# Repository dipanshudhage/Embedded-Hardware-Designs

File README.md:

# Embedded-Hardware-Designs

A collection of KiCad schematics, PCB layouts, 3D renders, STEP models, and hardware design files covering microcontroller boards, power/switching modules, USB-serial interfaces, LED controllers, and analog circuits.

## Repository Contents

| Folder | Description | Documentation & Assets |
| :--- | :--- | :--- |
| `ARDUINO MCU BOARD` | Microcontroller board design | [Project README](ARDUINO%20MCU%20BOARD/README.md) · `ASSETS/` |
| `ARDUINO PRO MINI` | Compact Arduino Pro Mini hardware layout | [Project README](ARDUINO%20PRO%20MINI/README.md) · `ASSETS/` · `.csv` |
| `LED` | LED circuit schematic, PCB layout, and 3D views | [Project README](LED/README.md) · `ASSETS/` |
| `LED FLASHING CIRCUIT` | Flashing LED circuit schematic and layout | [Project README](LED%20FLASHING%20CIRCUIT/README.md) · `ASSETS/` |
| `LED sequential flasher` | Sequential LED flasher circuit design | [Project README](LED%20sequential%20flasher/README.md) · `ASSETS/` |
| `Light-Activated LED Controller` | Light-triggered LED control circuit | [Project README](Light-Activated%20LED%20Controller/README.md) · `ASSETS/` |
| `Qwiic_Power_Switch` | Power switching hardware module | [Project README](Qwiic_Power_Switch/README.md) · `Assets/` |
| `SMART NODE – ESP32 ROOM CONTROLLER` | ESP32-based room controller hardware design | [Project README](SMART%20NODE%20%E2%80%93%20ESP32%20ROOM%20CONTROLLER/README.md) · `ASSETS/` |
| `Serial-Basic-CH340C-and-USBC` | USB-C to UART serial interface using CH340C | [Project README](Serial-Basic-CH340C-and-USBC/README.md) · `Assets/` |
| `TSH82 Configurable Op-Amp Board` | Configurable operational amplifier board using TSH82 | [Project README](TSH82%20Configurable%20Op-Amp%20Board/README.md) · `Assets/` |

## Tools & Workflow
* **EDA Suite:** KiCad (`.kicad_pro`, `.kicad_sch`, `.kicad_pcb`)
* **Visuals & 3D CAD:** Schematic, layout, and front/back 3D PNG renders plus `.step` 3D models

## How to Use
1. Browse any project folder's `README.md` for a quick look at its schematic, PCB layout, and 3D front/back views.
2. Open the `.kicad_pro` file in **KiCad** to inspect schematics, footprints, and board layouts.
3. Run Electrical Rule Checks (ERC) and Design Rule Checks (DRC) and verify component ratings/footprints before fabrication or assembly.

## Hardware & Safety Disclaimer
These schematic, PCB, and hardware files are shared for educational, learning, and prototyping purposes. Always review schematics, power ratings, isolation clearances, and component datasheets carefully before powering up or manufacturing any circuit.

## License
This repository is licensed under the **MIT License** — see the [`LICENSE`](LICENSE) file for details.

## Author
**Dipanshu Dhage**

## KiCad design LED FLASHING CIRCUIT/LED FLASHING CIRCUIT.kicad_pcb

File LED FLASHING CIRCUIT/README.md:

# LED FLASHING CIRCUIT

## Overview
LED flashing circuit designed in KiCad with schematic, board layout, and 3D renders.

## Schematic & PCB Layout

## 3D Board Views
| Front View | Back View |
| :---: | :---: |
|  |  |

## 3D CAD Model
* STEP Model: [`LED FLASHING CIRCUIT.step`](ASSETS/LED%20FLASHING%20CIRCUIT.step)

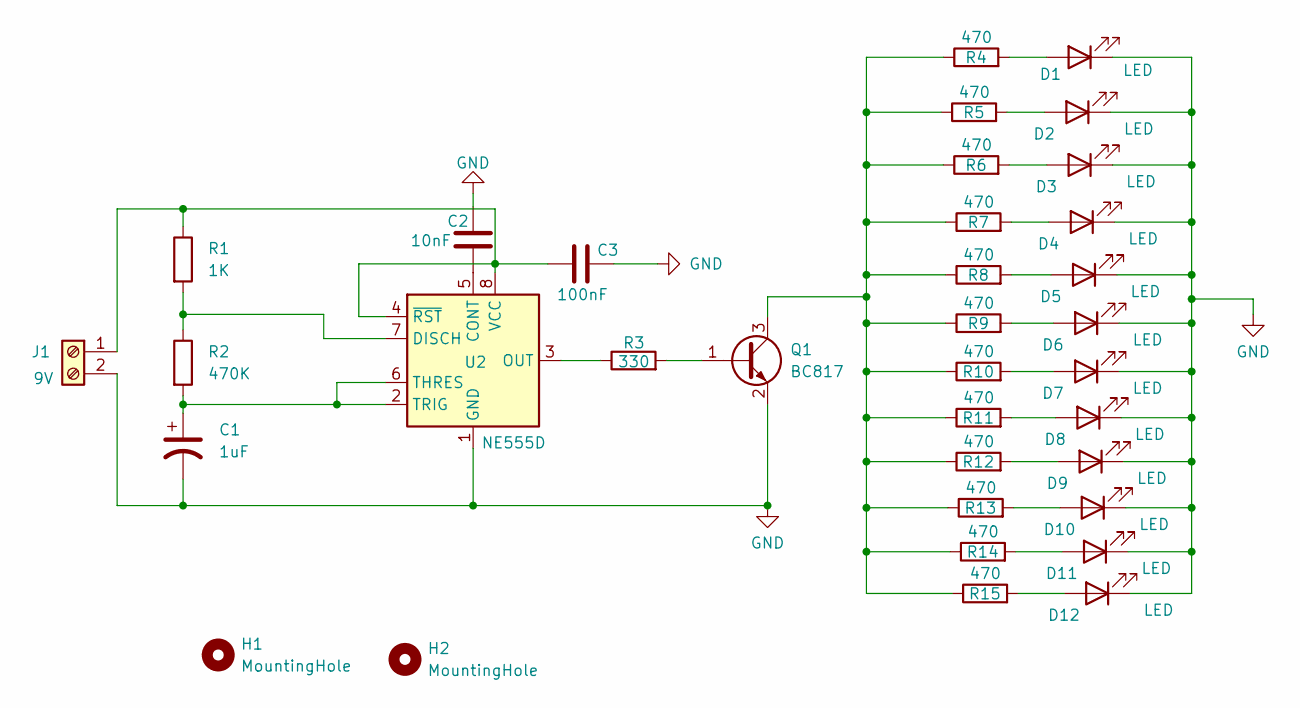
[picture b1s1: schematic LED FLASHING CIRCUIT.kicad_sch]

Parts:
C1: 1uF; C_0805_2012Metric
C2: 10nF; C_0805_2012Metric
C3: 100nF; C_0805_2012Metric
D1, D2, D3, D4, D5, D6, D7, D8, D9, D10, D11, D12: LED; LED_0805_2012Metric
H1, H2: MountingHole; MountingHole_2.2mm_M2
J1: 9V; JST_EH_S2B-EH_1x02_P2.50mm_Horizontal
Q1: BC817; SOT-23
R1: 1K; R_0805_2012Metric
R2: 470K; R_0805_2012Metric
R3: 330; R_0805_2012Metric
R4, R5, R6, R7, R8, R9, R10, R11, R12, R13, R14, R15: 470; R_0805_2012Metric
U2: NE555D; SOIC-8_3.9x4.9mm_P1.27mm

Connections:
GND: C1.2, C2.1, C3.1, D1.1 (K), D2.1 (K), D3.1 (K), D4.1 (K), D5.1 (K), D6.1 (K), D7.1 (K), D8.1 (K), D9.1 (K), D10.1 (K), D11.1 (K), D12.1 (K), J1.2, Q1.2 (E), U2.1 (GND)
unnamed: D1.2 (A), R4.2
unnamed: D2.2 (A), R5.2
unnamed: D3.2 (A), R6.2
unnamed: D4.2 (A), R7.2
unnamed: D5.2 (A), R8.2
unnamed: D6.2 (A), R9.2
unnamed: D7.2 (A), R10.2
unnamed: D8.2 (A), R11.2
unnamed: D9.2 (A), R12.2
unnamed: D10.2 (A), R13.2
unnamed: D11.2 (A), R14.2
unnamed: D12.2 (A), R15.2
unnamed: C3.2, J1.1, R1.1, U2.4 (~RST), U2.8 (VCC)
unnamed: Q1.1 (B), R3.2
unnamed: Q1.3 (C), R4.1, R5.1, R6.1, R7.1, R8.1, R9.1, R10.1, R11.1, R12.1, R13.1, R14.1, R15.1
unnamed: C2.2, U2.5 (CONT)
unnamed: R1.2, R2.1, U2.7 (DISCH)
unnamed: R3.1, U2.3 (OUT)
unnamed: C1.1, R2.2, U2.2 (TRIG), U2.6 (THRES)

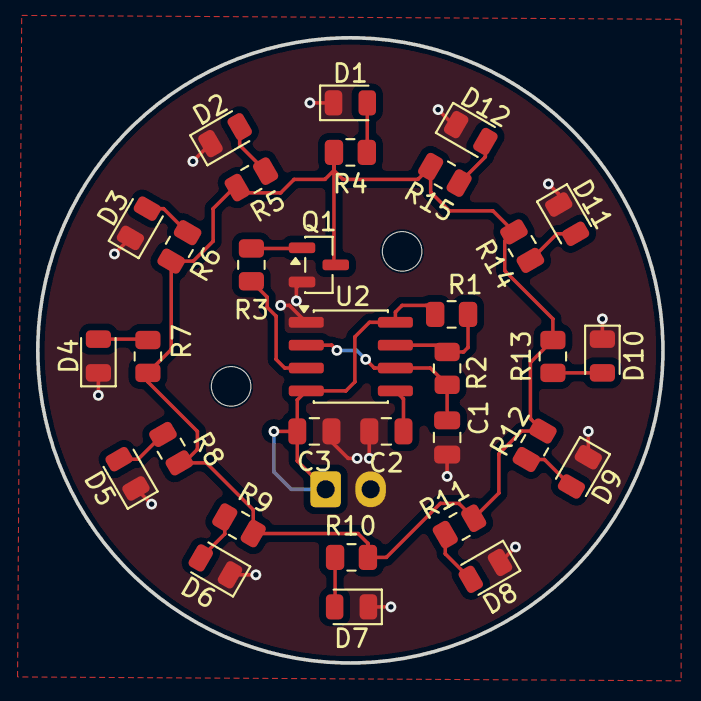
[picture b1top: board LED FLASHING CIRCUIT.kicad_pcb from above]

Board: 2 copper layers, 34.7 x 34.7 mm, 35 parts (1 on the bottom side), 20 nets.

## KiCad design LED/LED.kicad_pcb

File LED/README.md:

# LED

## Overview
LED hardware circuit design in KiCad with schematic, layout, and 3D views.

## Schematic & PCB Layout

## 3D Board Views
| Front View | Back View |
| :---: | :---: |
|  |  |

## 3D CAD Model
* STEP Model: [`LED.step`](ASSETS/LED.step)

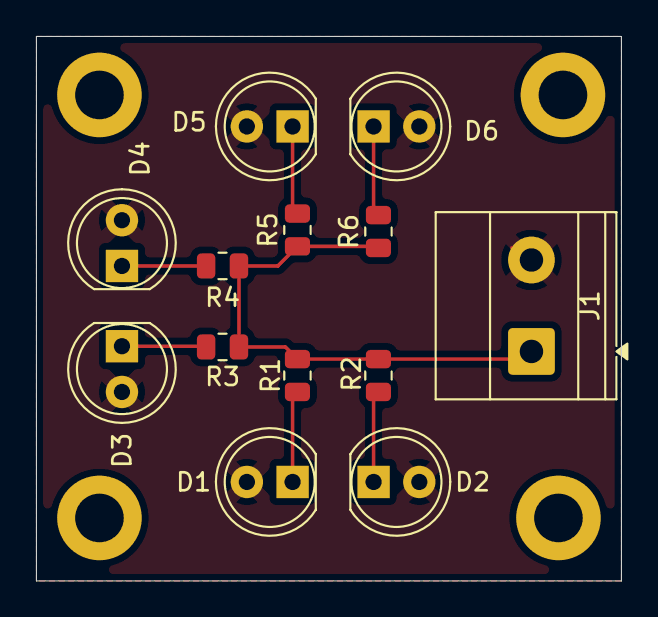
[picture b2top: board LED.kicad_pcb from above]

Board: 2 copper layers, 32.5 x 30.2 mm, 17 parts (0 on the bottom side), 8 nets.

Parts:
D1, D2, D3, D4, D5, D6: LED; LED_D5.0mm
H4, H4#2, H4#3, H4#4: MountingHole; MountingHole_2.7mm_M2.5_DIN965_Pad
J1: Power Source; TerminalBlock_Phoenix_MKDS-1,5-2-5.08_1x02_P5.08mm_Horizont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
R1, R2, R3, R4, R5, R6: 15; R_0805_2012Metric

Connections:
+3.3V: J1.1, R1.1, R2.1, R3.1, R4.1, R5.1, R6.1
GND: D1.2 (A), D2.2 (A), D3.2 (A), D4.2 (A), D5.2 (A), D6.2 (A), J1.2
unnamed: D1.1 (K), R1.2
unnamed: D2.1 (K), R2.2
unnamed: D3.1 (K), R3.2
unnamed: D4.1 (K), R4.2
unnamed: D5.1 (K), R5.2
unnamed: D6.1 (K), R6.2

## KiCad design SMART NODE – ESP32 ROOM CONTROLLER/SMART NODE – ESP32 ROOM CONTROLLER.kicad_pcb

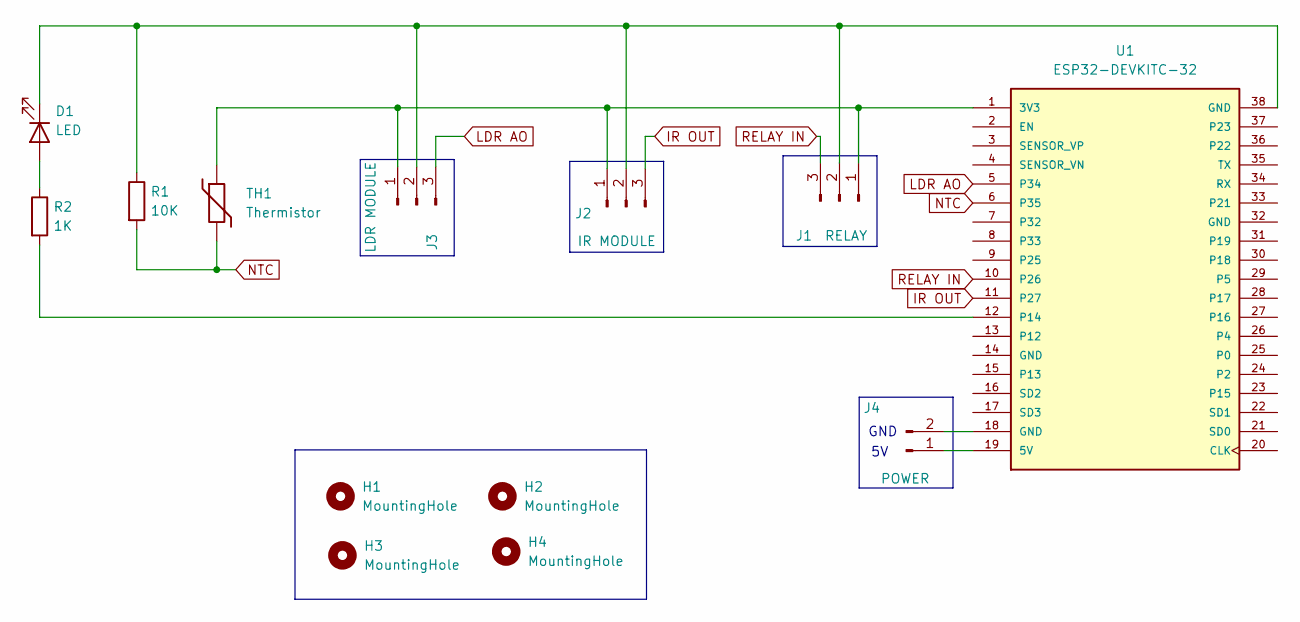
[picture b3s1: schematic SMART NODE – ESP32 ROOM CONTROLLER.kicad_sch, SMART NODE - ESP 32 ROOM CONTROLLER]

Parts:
D1: LED; LED_D5.0mm
H1, H2, H3, H4: MountingHole; MountingHole_2.2mm_M2
J1: RELAY; PinSocket_1x03_P2.54mm_Vertical
J2: IR MODULE; PinSocket_1x03_P2.54mm_Vertical
J3: LDR MODULE; PinSocket_1x03_P2.54mm_Vertical
J4: POWER; TerminalBlock_Phoenix_MKDS-1,5-2_1x02_P5.00mm_Horizontal
R1: 10K; R_Axial_DIN0207_L6.3mm_D2.5mm_P10.16mm_Horizontal
R2: 1K; R_Axial_DIN0207_L6.3mm_D2.5mm_P10.16mm_Horizontal
TH1: Thermistor; C_Disc_D5.0mm_W2.5mm_P2.50mm
U1: ESP32-DEVKITC-32; ESP32 DEVKIT

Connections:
IR OUT: J2.3, U1.11 (P27)
LDR AO: J3.3, U1.5 (P34)
NTC: R1.2, TH1.2, U1.6 (P35)
unnamed: D1.2 (A), R2.1
unnamed: D1.1 (K), J1.2, J2.2, J3.2, R1.1, U1.38 (GND)
unnamed: J1.1, J2.1, J3.1, TH1.1, U1.1 (3V3)
unnamed: J4.1, U1.19 (5V)
unnamed: J4.2, U1.18 (GND)
unnamed: R2.2, U1.12 (P14)
RELAY IN: J1.3, U1.10 (P26)

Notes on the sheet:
GND

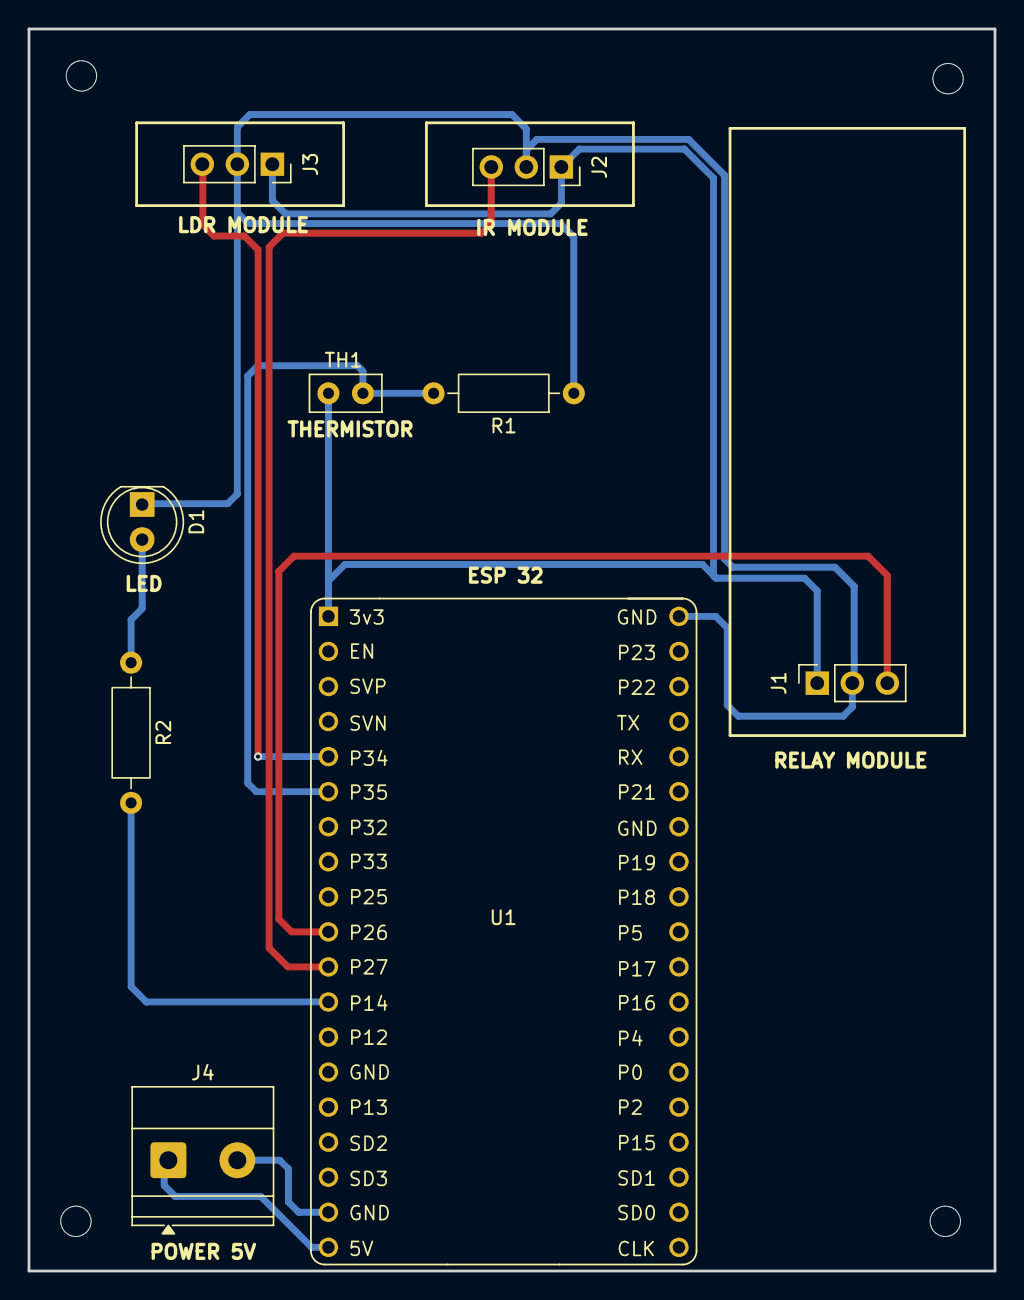
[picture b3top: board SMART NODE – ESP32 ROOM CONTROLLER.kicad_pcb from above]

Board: 2 copper layers, 70.0 x 90.0 mm, 13 parts (0 on the bottom side), 10 nets.

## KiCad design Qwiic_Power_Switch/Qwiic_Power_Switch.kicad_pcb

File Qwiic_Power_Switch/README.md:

# Qwiic_Power_Switch

## Overview
Power switching hardware module with schematic, PCB layout, and 3D views.

## Schematic & PCB Layout

## 3D Board Views
| Front View | Back View |
| :---: | :---: |
|  |  |

## 3D CAD Model
* STEP Model: [`Qwiic_Power_Switch.step`](Assets/Qwiic_Power_Switch.step)

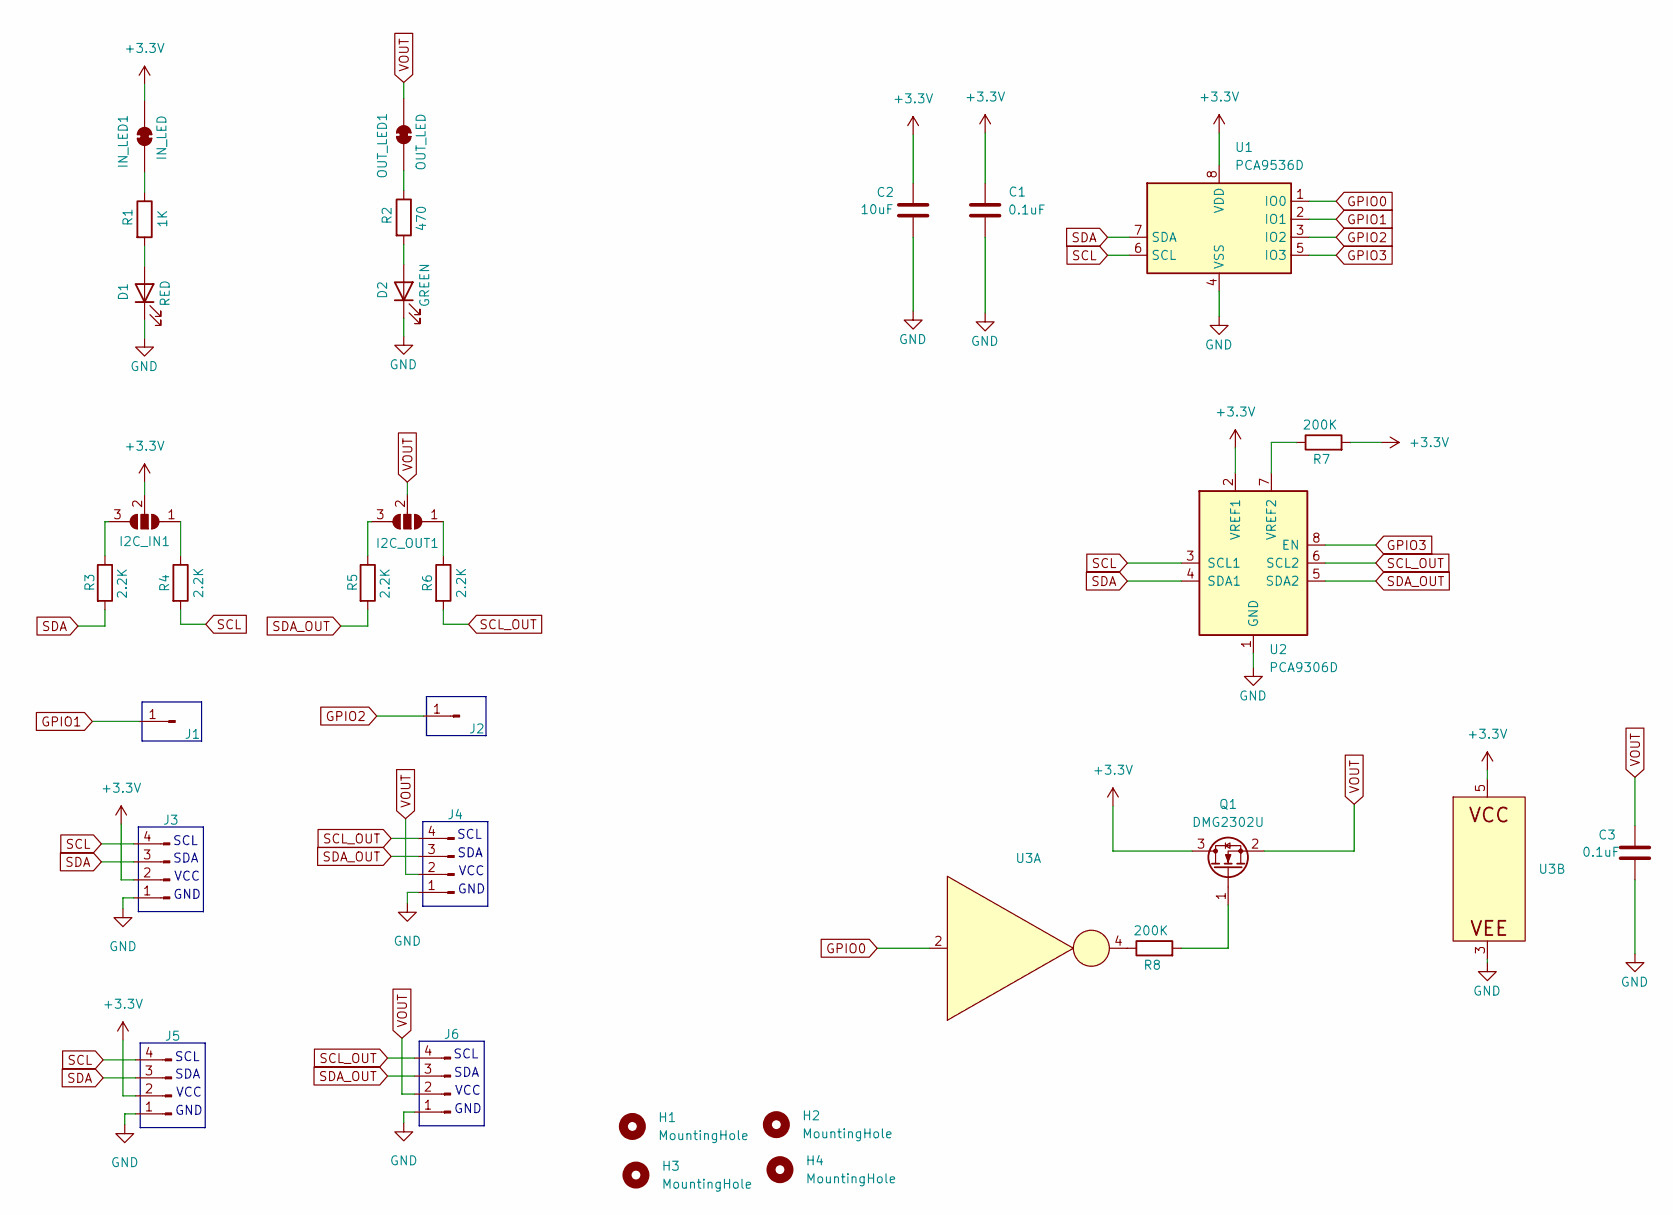
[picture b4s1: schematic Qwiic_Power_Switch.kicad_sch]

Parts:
C1, C3: 0.1uF; C_0603_1608Metric
C2: 10uF; C_0805_2012Metric
D1: RED; LED_0603_1608Metric
D2: GREEN; LED_0603_1608Metric
H1, H2, H3, H4: MountingHole; MountingHole_2.2mm_M2
I2C_IN1, I2C_OUT1: SolderJumper_3_Open; SolderJumper-3_P1.3mm_Open_Pad1.0x1.5mm
IN_LED1: IN_LED; LED_0603_1608Metric
J1, J2: Conn_01x01_Pin; PinHeader_1x01_P2.54mm_Vertical
J3, J4, J5, J6: Conn_01x04_Pin; PinSocket_1x04_P2.54mm_Vertical
OUT_LED1: OUT_LED; LED_0603_1608Metric
Q1: DMG2302U; SOT-23
R1: 1K; R_0603_1608Metric
R2: 470; R_0603_1608Metric
R3, R4, R5, R6: 2.2K; R_0603_1608Metric
R7, R8: 200K; R_0603_1608Metric
U1: PCA9536D; SOIC-8_3.9x4.9mm_P1.27mm
U2: PCA9306D; SO-8_3.9x4.9mm_P1.27mm
U3: SOT-353_SC-70-5

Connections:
+3.3V: C1.1, C2.1, I2C_IN1.2 (C), IN_LED1.2 (B), J3.2, J5.2, Q1.3 (D), R7.2, U1.8 (VDD), U2.2 (VREF1), U3.5
GND: C1.2, C2.2, C3.2, D1.1 (K), D2.1 (K), J3.1, J4.1, J5.1, J6.1, U1.4 (VSS), U2.1 (GND), U3.3
GPIO0: U1.1 (IO0), U3.2
GPIO1: J1.1 (Pin_1_1), U1.2 (IO1)
GPIO2: J2.1 (Pin_1_1), U1.3 (IO2)
GPIO3: U1.5 (IO3), U2.8 (EN)
unnamed: D1.2 (A), R1.2
unnamed: D2.2 (A), R2.2
unnamed: I2C_IN1.1 (A), R4.1
unnamed: I2C_IN1.3 (B), R3.1
unnamed: I2C_OUT1.1 (A), R6.1
unnamed: I2C_OUT1.3 (B), R5.1
unnamed: IN_LED1.1 (A), R1.1
unnamed: OUT_LED1.1 (A), R2.1
unnamed: Q1.1 (G), R8.2
unnamed: R8.1, U3.4
unnamed: R7.1, U2.7 (VREF2)
SCL: J3.4, J5.4, R4.2, U1.6 (SCL), U2.3 (SCL1)
SCL_OUT: J4.4, J6.4, R6.2, U2.6 (SCL2)
SDA: J3.3, J5.3, R3.2, U1.7 (SDA), U2.4 (SDA1)
SDA_OUT: J4.3, J6.3, R5.2, U2.5 (SDA2)
VOUT: C3.1, I2C_OUT1.2 (C), J4.2, J6.2, OUT_LED1.2 (B), Q1.2 (S)

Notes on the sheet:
VCC
SDA
SCL
GND

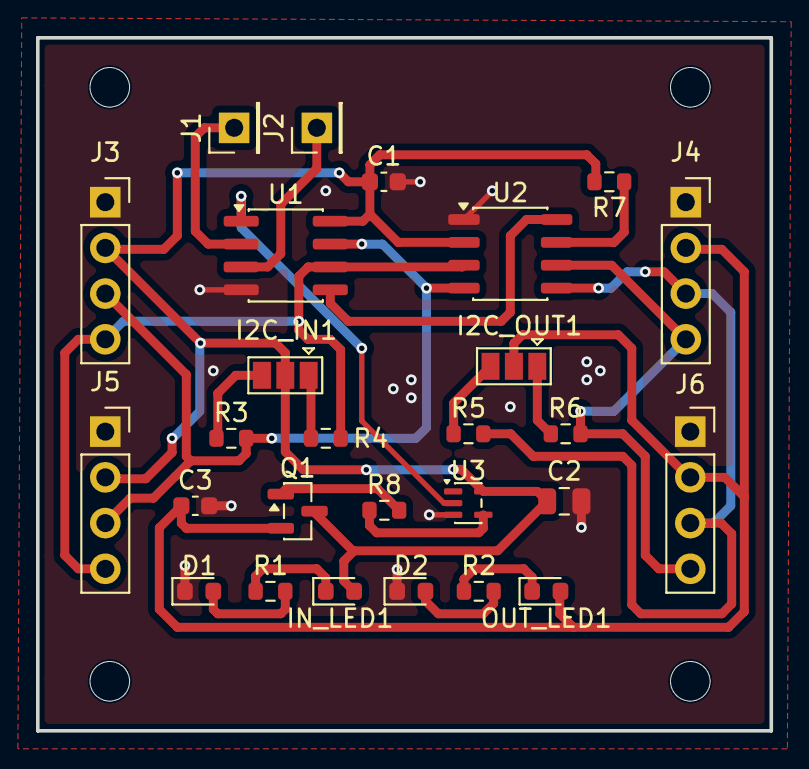
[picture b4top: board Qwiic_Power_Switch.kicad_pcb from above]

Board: 2 copper layers, 40.8 x 38.5 mm, 31 parts (0 on the bottom side), 22 nets.

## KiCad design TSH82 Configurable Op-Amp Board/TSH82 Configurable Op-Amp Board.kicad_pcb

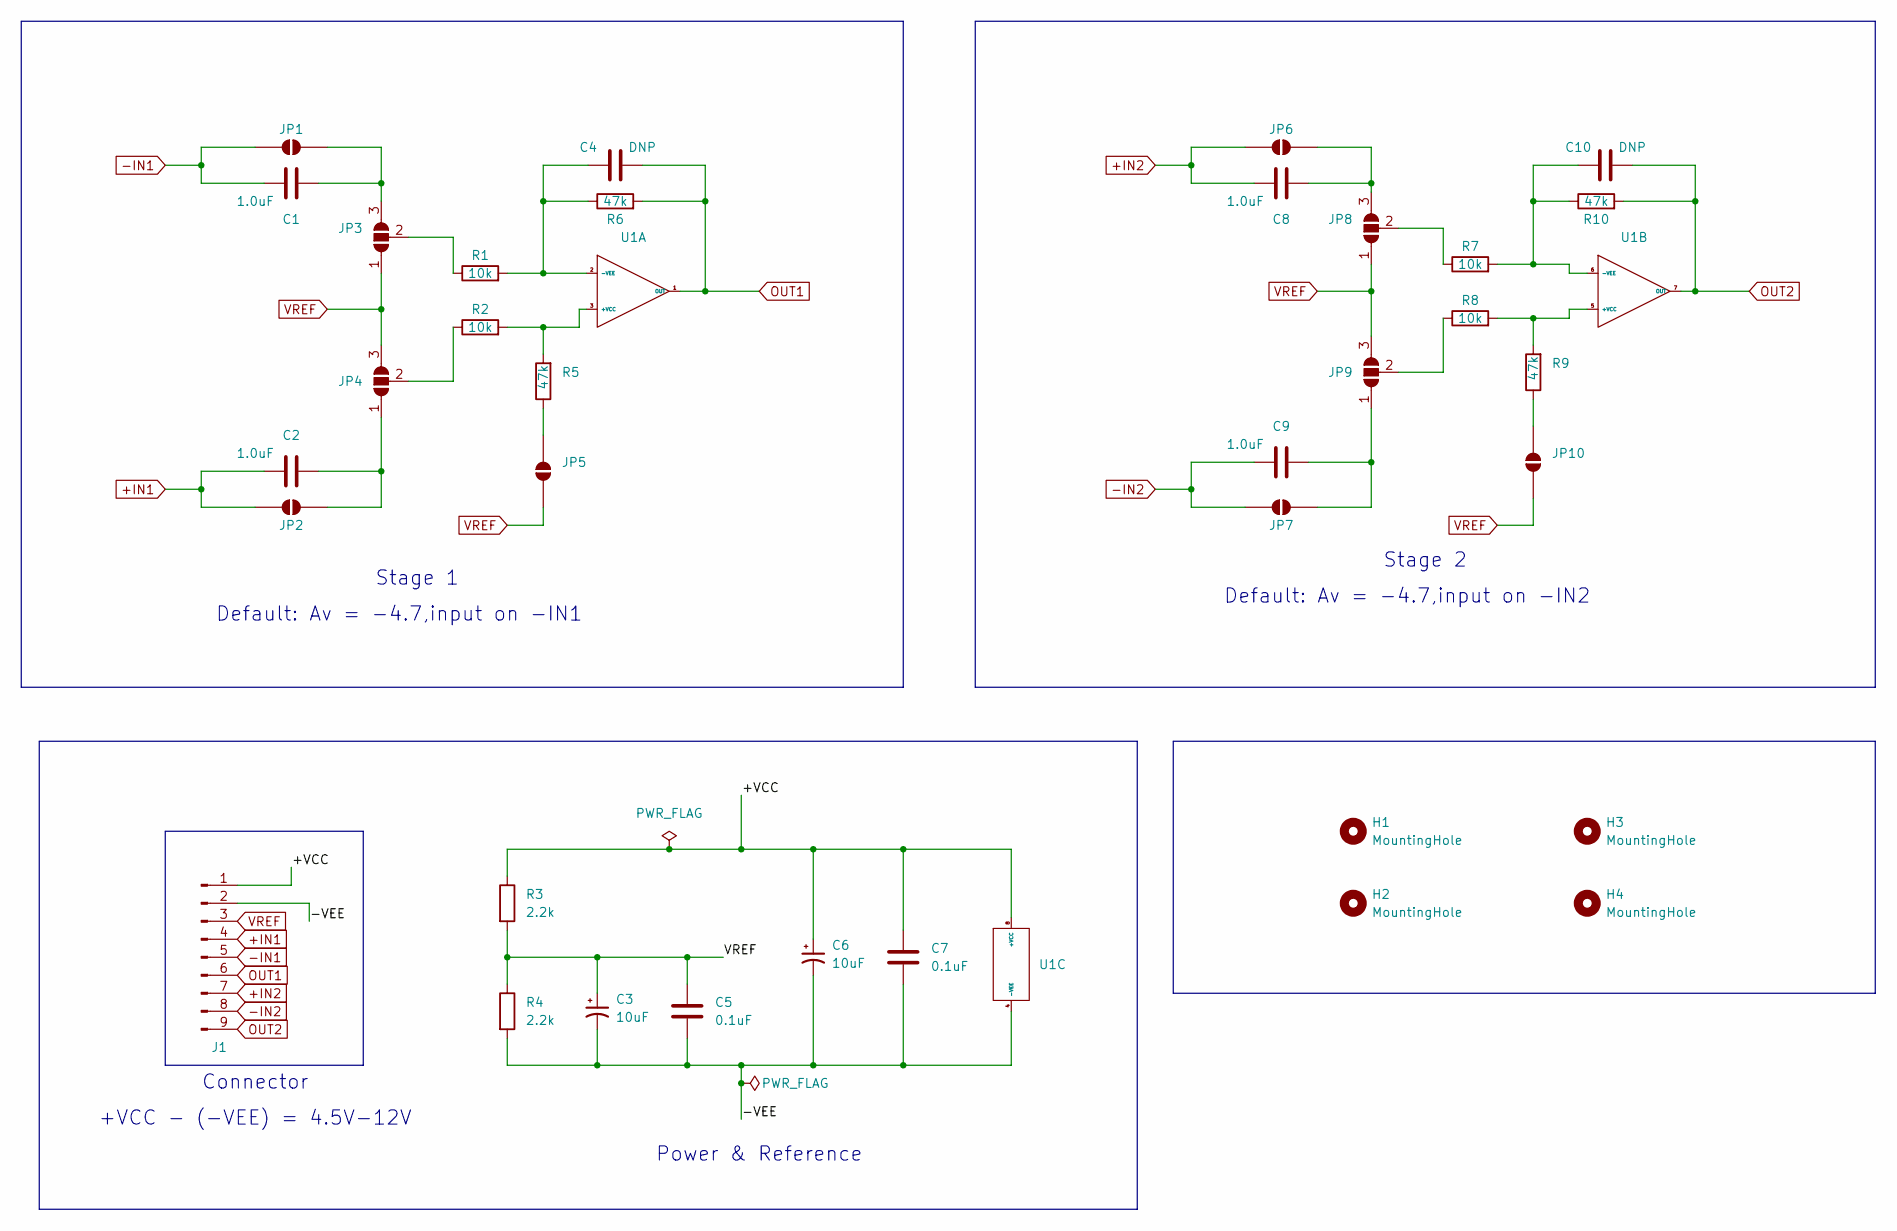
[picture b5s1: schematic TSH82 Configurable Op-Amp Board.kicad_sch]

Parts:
C1, C2, C8, C9: 1.0uF; C_0805_2012Metric
C3, C6: 10uF; C_1206_3216Metric
C4, C10: DNP; C_0805_2012Metric
C5, C7: 0.1uF; C_0805_2012Metric
H1, H2, H3, H4: MountingHole; MountingHole_2.7mm
J1: Conn_01x09_Pin; PinHeader_1x09_P2.54mm_Vertical
JP1, JP5, JP6, JP10: SolderJumper_2_Open; SolderJumper-2_P1.3mm_Open_Pad1.0x1.5mm
JP2, JP7: SolderJumper-2_P1.3mm_Open_Pad1.0x1.5mm
JP3, JP4, JP8, JP9: SolderJumper_3_Open; SolderJumper-3_P1.3mm_Open_Pad1.0x1.5mm
R1, R2, R7, R8: 10k; R_0805_2012Metric
R3, R4: 2.2k; R_0805_2012Metric
R5, R6, R9, R10: 47k; R_0805_2012Metric
U1: SOIC-8_3.9x4.9mm_P1.27mm

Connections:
+IN1: C2.1, J1.4, JP2.1 (A)
+IN2: C8.1, J1.7, JP6.1 (A)
-IN1: C1.1, J1.5, JP1.1 (A)
-IN2: C9.1, J1.8, JP7.1 (A)
/+VCC: C6.1, C7.1, J1.1, R3.1, U1.8 (+VCC)
/-VEE: C3.2, C5.2, C6.2, C7.2, J1.2, R4.2, U1.4 (-VEE)
unnamed: C1.2, JP1.2 (B), JP3.3 (B)
unnamed: C2.2, JP2.2 (B), JP4.1 (A)
unnamed: JP3.2 (C), R1.1
unnamed: JP4.2 (C), R2.1
unnamed: JP5.2 (B), R5.1
unnamed: C8.2, JP6.2 (B), JP8.3 (B)
unnamed: C9.2, JP7.2 (B), JP9.1 (A)
unnamed: JP8.2 (C), R7.1
unnamed: JP9.2 (C), R8.1
unnamed: JP10.2 (B), R9.1
unnamed: R2.2, R5.2, U1.3 (+VCC)
unnamed: C4.1, R1.2, R6.1, U1.2 (-VEE)
unnamed: R8.2, R9.2, U1.5 (+VCC)
unnamed: C10.1, R7.2, R10.1, U1.6 (-VEE)
OUT1: C4.2, J1.6, R6.2, U1.1 (OUT)
OUT2: C10.2, J1.9, R10.2, U1.7 (OUT)
VREF: C3.1, C5.1, J1.3, JP3.1 (A), JP4.3 (B), JP5.1 (A), JP8.1 (A), JP9.3 (B), JP10.1 (A), R3.2, R4.1

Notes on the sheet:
Default: Av = -4.7,input on -IN2
Stage 2
Connector
+VCC - (-VEE) = 4.5V-12V
Default: Av = -4.7,input on -IN1
Power & Reference
Stage 1

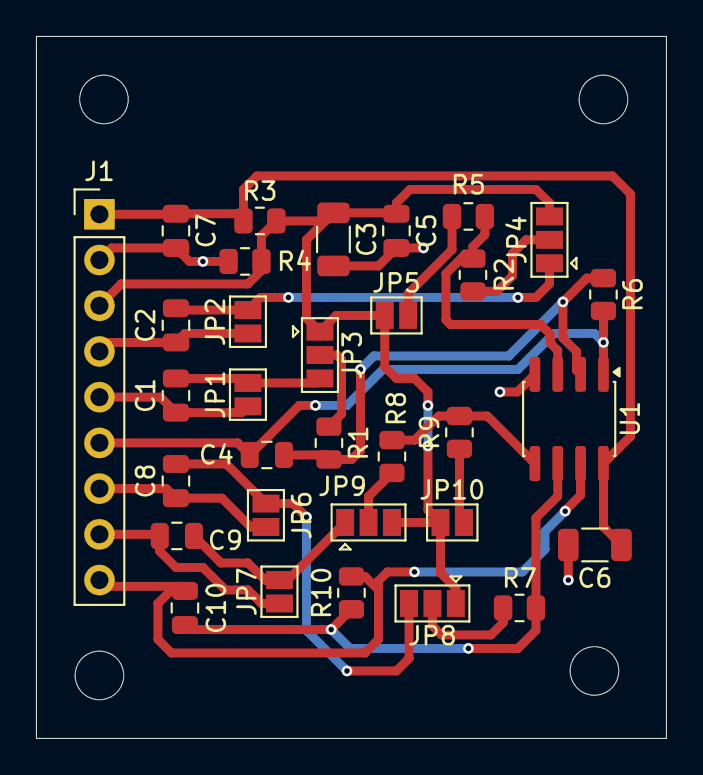
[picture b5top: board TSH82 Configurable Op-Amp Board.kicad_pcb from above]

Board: 2 copper layers, 35.0 x 39.0 mm, 36 parts (0 on the bottom side), 23 nets.

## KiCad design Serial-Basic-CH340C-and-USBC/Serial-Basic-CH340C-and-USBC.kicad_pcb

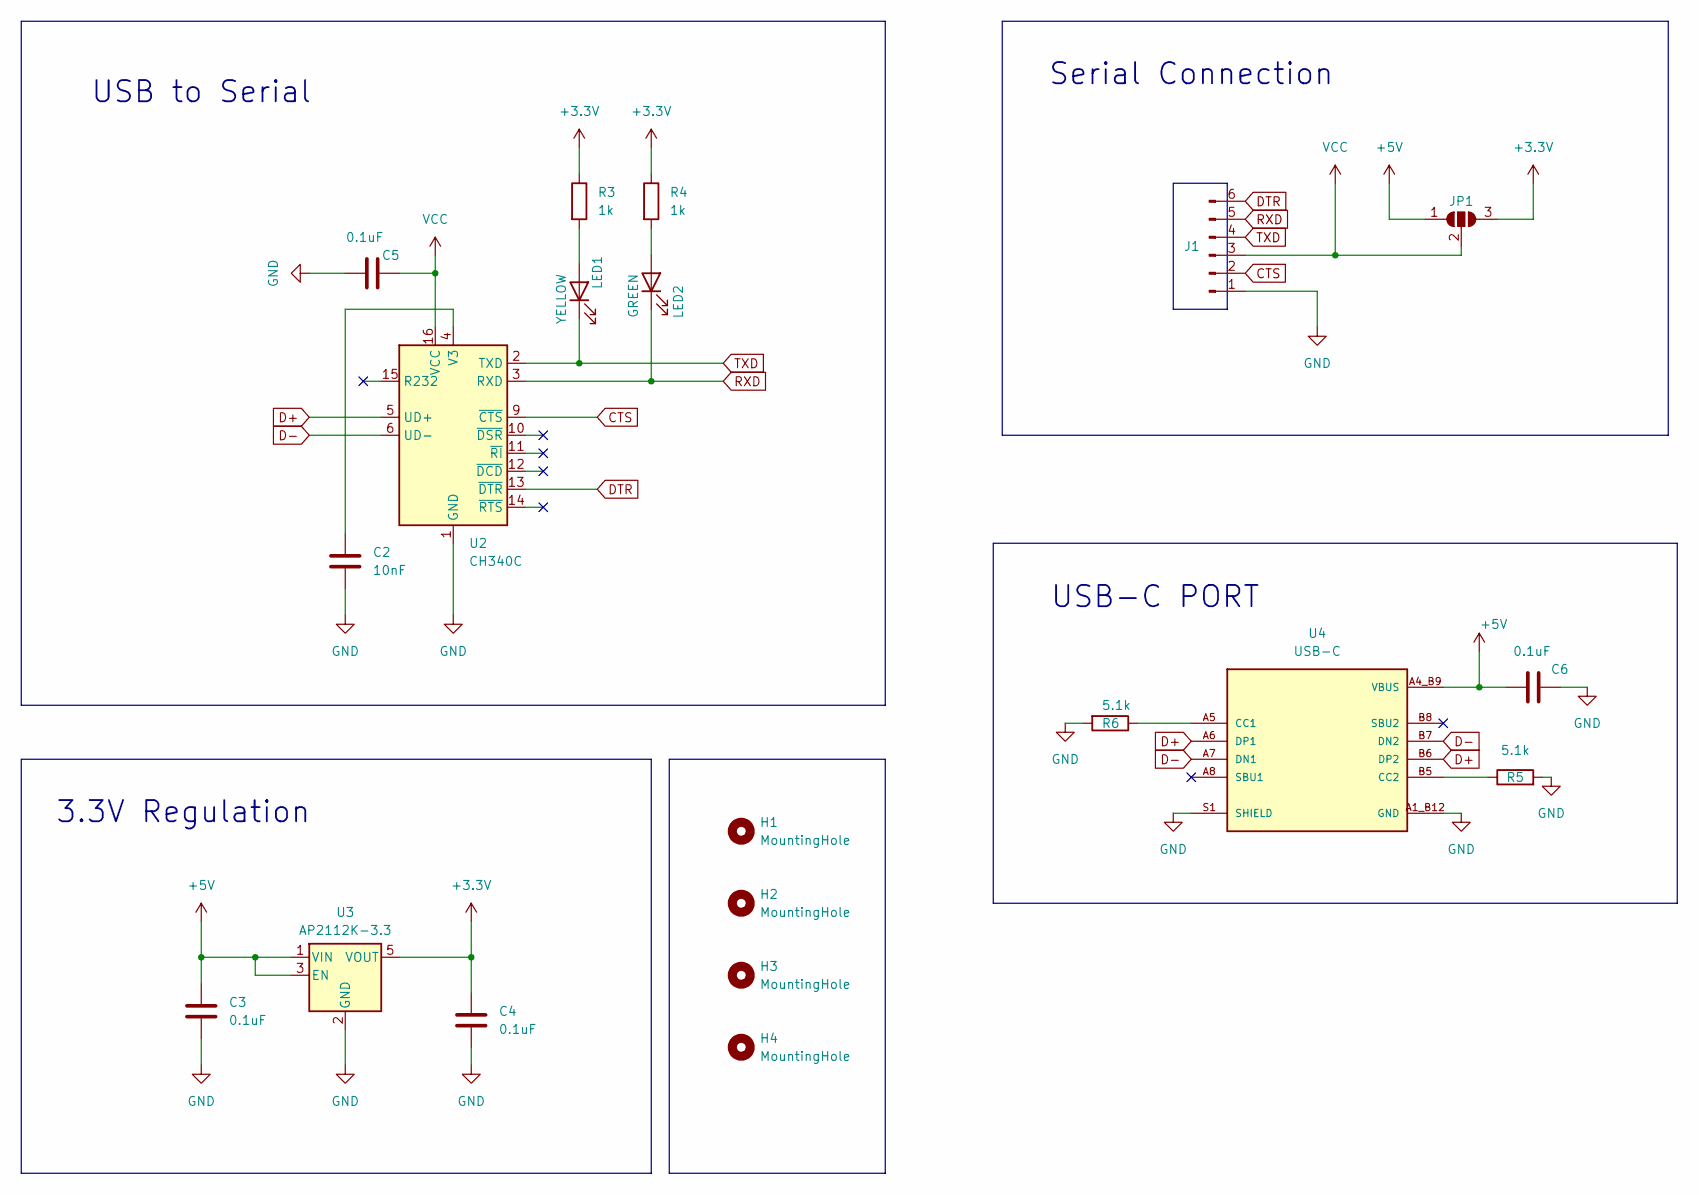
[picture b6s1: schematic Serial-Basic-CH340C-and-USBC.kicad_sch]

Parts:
C2: 10nF; C_0805_2012Metric
C3, C4, C5, C6: 0.1uF; C_0805_2012Metric
H1, H2, H3, H4: MountingHole; MountingHole_2.2mm_M2
J1: Conn_01x06_Pin; PinHeader_1x06_P2.54mm_Vertical
JP1: SolderJumper_3_Open; SolderJumper-3_P1.3mm_Open_Pad1.0x1.5mm
LED1: YELLOW; LED_0805_2012Metric
LED2: GREEN; LED_0805_2012Metric
R3, R4: 1k; R_0805_2012Metric
R5, R6: 5.1k; R_0805_2012Metric
U2: CH340C; SOIC-16_3.9x9.9mm_P1.27mm
U3: AP2112K-3.3; SOT-23-5
U4: USB-C

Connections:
+3.3V: C4.1, JP1.3 (B), R3.1, R4.1, U3.5 (VOUT)
+5V: C3.1, C6.1, JP1.1 (A), U3.1 (VIN), U3.3 (EN), U4.A4_B9 (VBUS), U4.B4_A9 (VBUS)
CTS: J1.2, U2.9 (~CTS)
D+: U2.5 (UD+), U4.A6 (DP1), U4.B6 (DP2)
D-: U2.6 (UD-), U4.A7 (DN1), U4.B7 (DN2)
DTR: J1.6, U2.13 (~DTR)
GND: C2.2, C3.2, C4.2, C5.2, C6.2, J1.1, R5.2, R6.2, U2.1 (GND), U3.2 (GND), U4.A1_B12 (GND), U4.B1_A12 (GND), U4.S1 (SHIELD), U4.S2 (SHIELD), U4.S3 (SHIELD), U4.S4 (SHIELD)
unnamed: LED1.2 (A), R3.2
unnamed: LED2.2 (A), R4.2
unnamed: C2.1, U2.4 (V3)
unnamed: R6.1, U4.A5 (CC1)
unnamed: R5.1, U4.B5 (CC2)
RXD: J1.5, LED2.1 (K), U2.3 (RXD)
TXD: J1.4, LED1.1 (K), U2.2 (TXD)
VCC: C5.1, J1.3, JP1.2 (C), U2.16 (VCC)

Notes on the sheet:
USB to Serial
3.3V Regulation
USB-C PORT
Serial Connection

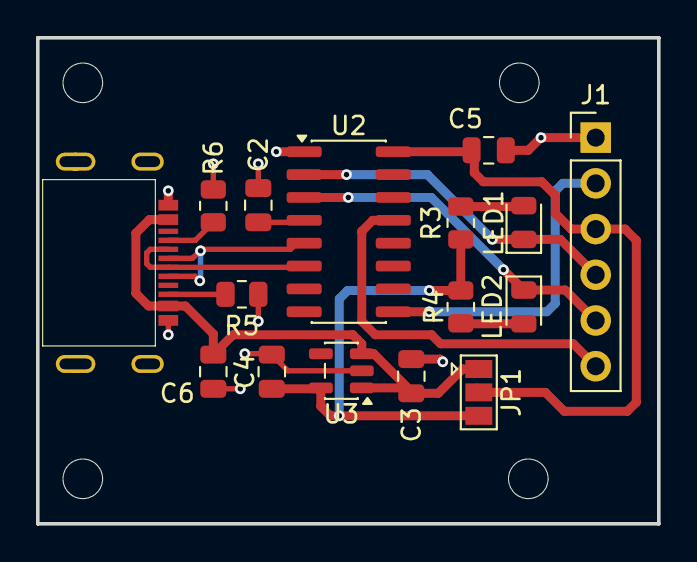
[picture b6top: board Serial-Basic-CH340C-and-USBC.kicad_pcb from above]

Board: 2 copper layers, 34.5 x 27.0 mm, 20 parts (0 on the bottom side), 15 nets.

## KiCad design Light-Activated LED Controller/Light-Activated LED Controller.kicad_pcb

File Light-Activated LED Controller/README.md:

# Light-Activated LED Controller

## Overview
Light-activated LED controller circuit with KiCad schematic, PCB layout, and 3D renders.

## Schematic & PCB Layout

## 3D Board Views
| Front View | Back View |
| :---: | :---: |
|  |  |

## 3D CAD Model
* STEP Model: [`Light-Activated LED Controller.step`](ASSETS/Light-Activated%20LED%20Controller.step)

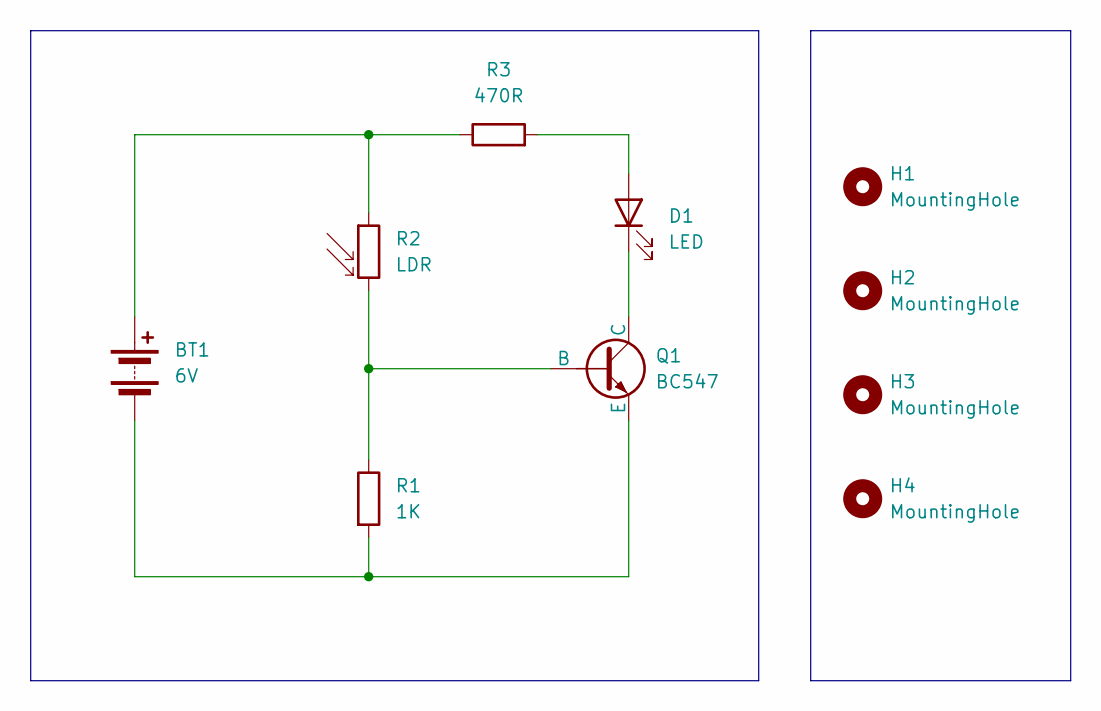
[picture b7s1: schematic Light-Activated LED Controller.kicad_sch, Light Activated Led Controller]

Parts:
BT1: 6V; JST_PH_B2B-PH-K_1x02_P2.00mm_Vertical
D1: LED; LED_D5.0mm
H1, H2, H3, H4: MountingHole; MountingHole_2.7mm
Q1: BC547; TO-92_Inline
R1: 1K; R_Axial_DIN0207_L6.3mm_D2.5mm_P7.62mm_Horizontal
R2: LDR; R_LDR_5.1x4.3mm_P3.4mm_Vertical
R3: 470R; R_Axial_DIN0207_L6.3mm_D2.5mm_P7.62mm_Horizontal

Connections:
unnamed: BT1.1 (+), R2.1, R3.1
unnamed: BT1.2 (-), Q1.3 (E), R1.2
unnamed: D1.2 (A), R3.2
unnamed: D1.1 (K), Q1.1 (C)
unnamed: Q1.2 (B), R1.1, R2.2

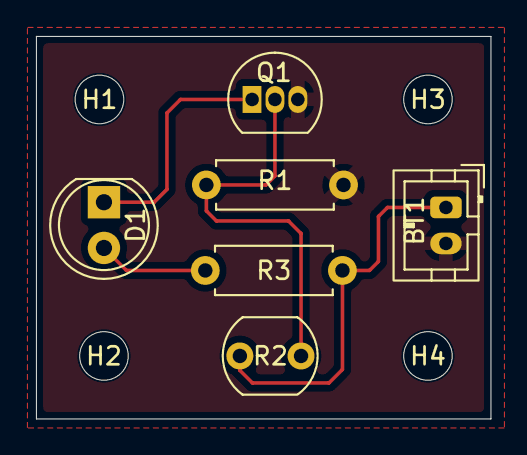
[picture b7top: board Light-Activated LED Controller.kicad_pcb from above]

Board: 2 copper layers, 25.2 x 21.2 mm, 10 parts (0 on the bottom side), 5 nets.

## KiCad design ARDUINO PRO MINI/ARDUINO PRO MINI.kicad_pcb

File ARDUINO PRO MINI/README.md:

# ARDUINO PRO MINI

## Overview
Compact Arduino Pro Mini hardware layout with KiCad project files, BOM/data CSV, and 3D assets.

## Schematic & PCB Layout

## 3D Board Views
| Front View | Back View |
| :---: | :---: |
|  |  |

## 3D CAD Model & Data
* STEP Model: [`ARDUINO PRO MINI.step`](ASSETS/ARDUINO%20PRO%20MINI.step)
* CSV Data: [`ARDUINO PRO MINI.csv`](ARDUINO%20PRO%20MINI.csv)

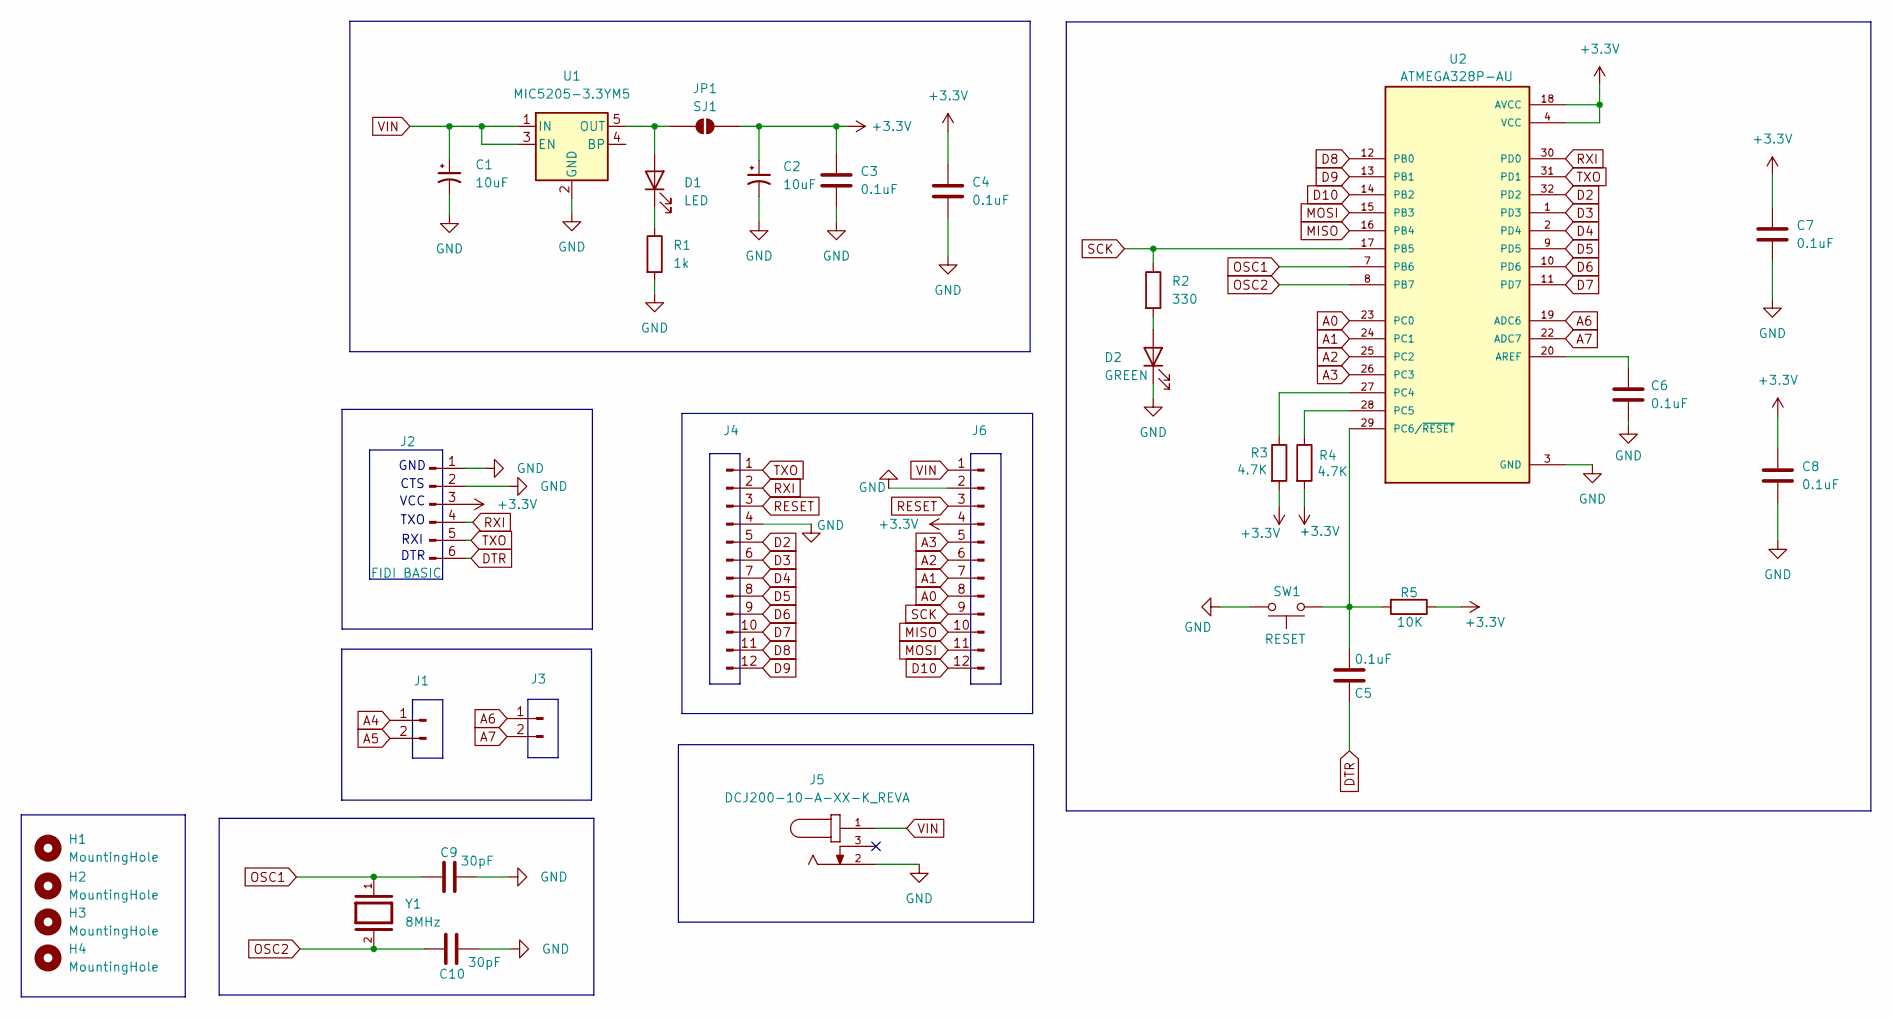
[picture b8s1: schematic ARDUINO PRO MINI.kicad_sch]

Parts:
C1, C2: 10uF; C_1206_3216Metric
C3, C4, C5, C6, C7, C8: 0.1uF; C_0805_2012Metric
C9, C10: 30pF; C_0805_2012Metric
D1: LED; LED_0805_2012Metric
D2: GREEN; LED_0805_2012Metric
H1, H2, H3, H4: MountingHole; MountingHole_2.2mm_M2
J1, J3: Conn_01x02_Pin; PinHeader_1x02_P2.54mm_Vertical
J2: FIDI BASIC; PinHeader_1x06_P2.54mm_Vertical
J4, J6: Conn_01x12_Pin; PinHeader_1x12_P2.54mm_Vertical
J5: DCJ200-10-A-XX-K_REVA; GCT_DCJ200-10-A-XX-K_REVA; PARTREV A
JP1: SJ1; SolderJumper-2_P1.3mm_Open_RoundedPad1.0x1.5mm
R1: 1k; R_0805_2012Metric
R2: 330; R_0805_2012Metric
R3, R4: 4.7K; R_0805_2012Metric
R5: 10K; R_0805_2012Metric
SW1: RESET; SW_SPST_TL3305A
U1: MIC5205-3.3YM5; SOT-23-5
U2: ATMEGA328P-AU; QFP80P900X900X120-32N; PARTREV 8271A
Y1: 8MHz; XTAL_ABM3-8.000MHZ-D2Y-T; MPN ABM3-8.000MHZ-D2Y-T

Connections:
+3.3V: C2.1, C3.1, C4.1, C7.1, C8.1, J2.3, J6.4, JP1.2 (B), R3.2, R4.2, R5.1, U2.4 (VCC), U2.6 (VCC), U2.18 (AVCC)
A0: J6.8, U2.23 (PC0)
A1: J6.7, U2.24 (PC1)
A2: J6.6, U2.25 (PC2)
A3: J6.5, U2.26 (PC3)
A4: J1.1
A5: J1.2
A6: J3.1, U2.19 (ADC6)
A7: J3.2, U2.22 (ADC7)
D2: J4.5, U2.32 (PD2)
D3: J4.6, U2.1 (PD3)
D4: J4.7, U2.2 (PD4)
D5: J4.8, U2.9 (PD5)
D6: J4.9, U2.10 (PD6)
D7: J4.10, U2.11 (PD7)
D8: J4.11, U2.12 (PB0)
D9: J4.12, U2.13 (PB1)
D10: J6.12, U2.14 (PB2)
DTR: C5.2, J2.6
GND: C1.2, C2.2, C3.2, C4.2, C6.2, C7.2, C8.2, C9.2, C10.2, D2.1 (K), J2.1, J2.2, J4.4, J5.2, J6.2, R1.2, SW1.1, U1.2 (GND), U2.3 (GND), U2.5 (GND), U2.21 (GND)
MISO: J6.10, U2.16 (PB4)
MOSI: J6.11, U2.15 (PB3)
unnamed: D1.2 (A), JP1.1 (A), U1.5 (OUT)
unnamed: D1.1 (K), R1.1
unnamed: D2.2 (A), R2.2
unnamed: C6.1, U2.20 (AREF)
unnamed: R3.1, U2.27 (PC4)
unnamed: R4.1, U2.28 (PC5)
unnamed: C5.1, R5.2, SW1.2, U2.29 (PC6/~RESET)
OSC1: C9.1, U2.7 (PB6), Y1.1
OSC2: C10.1, U2.8 (PB7), Y1.2
RESET: J4.3, J6.3
RXI: J2.4, J4.2, U2.30 (PD0)
SCK: J6.9, R2.1, U2.17 (PB5)
TXO: J2.5, J4.1, U2.31 (PD1)
VIN: C1.1, J5.1, J6.1, U1.1 (IN), U1.3 (EN)

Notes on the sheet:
DTR
RXI
GND
CTS
VCC
TXO
